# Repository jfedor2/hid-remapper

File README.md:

# HID Remapper

_For user documentation please see the project's website at [remapper.org](https://www.remapper.org/)._

This is a configurable USB dongle that allows you to remap inputs from mice, keyboards and other devices. It works completely in hardware and requires no software running on the computer during normal use.

It can do things like reassign buttons, change keyboard layouts, map mouse buttons to keyboard inputs, map keystrokes to mouse inputs, change mouse sensitivity (permanently or when a button is held), rotate mouse axes by arbitrary (non-90 degree) angles, drag-lock for mouse buttons, scroll by moving the mouse, and much more.

It is configurable [through a web browser](https://www.remapper.org/config/) using WebHID (Chrome or Chrome-based browser required).

Wireless receivers are supported and multiple devices can be connected at the same time using a USB hub (with different mappings for each device if desired).

In addition to the remapping functionality, it can do polling rate overclocking up to 1000 Hz.

A separate [serial](SERIAL.md) version of the remapper takes inputs from a serial (RS-232) mouse and translates them to USB.

There's also a [Bluetooth](BLUETOOTH.md) version that runs on nRF52840-based boards, which translates Bluetooth inputs to USB.

## How to make the device

There are three main ways of making the HID Remapper. You can either buy [this board](https://www.adafruit.com/product/5723) from Adafruit, make it yourself using a Raspberry Pi Pico (or two), or you can use the provided files to manufacture a custom board at JLCPCB or a similar service. The functionality is the same in all cases.

If you get the Feather RP2040 USB Host board from Adafruit, the device is ready to use, you just need to flash it with the right firmware ([remapper\_feather.uf2](https://github.com/jfedor2/hid-remapper/releases/latest/download/remapper_feather.uf2)). Hold the "Boot" button on the board, then press the "Reset" button. A USB drive should show up on your computer. Copy the UF2 file to that drive. That's it.

See [here](HARDWARE.md) for details on how to make the Pico variants of the device and [here](custom-boards/) for details on the custom board option.

## How to use the configuration tool

A live version of the web configuration tool can be found at [remapper.org/config](https://www.remapper.org/config/).

For details on how to use it, please see the [HID Remapper Manual](https://www.remapper.org/manual/).

If you can't use the browser-based configuration tool, there's also a [command-line tool](config-tool) that takes JSON in the same format as the web tool on standard input. I only tested it on Linux, but in theory it should also run on Windows and Mac.

## How to update the firmware

The procedure to update the firmware is similar on all variants. When you go to the configuration website and try to connect to your device when it doesn't have the latest firmware, you will get a message and a link to a version of the configuration interface that is compatible with your current (old) firmware. Click that link, connect to your HID Remapper by clicking "Open device" as usual, then go to the "Actions" tab and click "Flash firmware". This will put your device in firmware flashing mode. A drive should appear on your computer. For all the RP2040-based variants, the drive will be named "RPI-RP2". For the Bluetooth variants, it will be called something else, depending on what board you're using. Download the correct firmware file for your variant (see table below) and copy it to that drive. On custom boards v1, v2, v5, v6 and v7 (dual RP2040 boards), after flashing the firmware you have to disconnect and reconnect your HID Remapper. That's it, you can go back to the regular version of the configuration interface and carry on.

_(Please note that previously a manual "Flash B side" step was required on custom boards v1, v2, v5, v6 and v7. That is no longer necessary.)_

If you're using the dual Pico variant then you need to flash the A side using the [remapper\_dual\_a.uf2](https://github.com/jfedor2/hid-remapper/releases/latest/download/remapper_dual_a.uf2) file as described above and then flash the B side manually. Disconnect your HID Remapper from your computer, disconnect the OTG adapter from the B-side Pico, hold the BOOTSEL button on the B-side Pico and then, while holding the button, connect the B-side Pico to your computer. A drive named "RPI-RP2" should appear. Copy the [remapper\_dual\_b.uf2](https://github.com/jfedor2/hid-remapper/releases/latest/download/remapper_dual_b.uf2) file to that drive. Disconnect the B-side Pico from your computer, reconnect the OTG adapter and reconnect your HID Remapper to your computer.

When updating firmware, the current configuration on your HID Remapper is preserved. For extra peace of mind you can export your configuration to a JSON file before performing the update. That way if you need to revert to the old version of the firmware for any reason, you'll be able to import the configuration from the JSON file (configuration is lost when going from a newer firmware to an older firmware).

variant | firmware file(s) | notes
------- | ---------------- | -----------------------
single Pico | [remapper.uf2](https://github.com/jfedor2/hid-remapper/releases/latest/download/remapper.uf2) |
dual Pico | [remapper\_dual\_a.uf2](https://github.com/jfedor2/hid-remapper/releases/latest/download/remapper_dual_a.uf2)<br>[remapper\_dual\_b.uf2](https://github.com/jfedor2/hid-remapper/releases/latest/download/remapper_dual_b.uf2) | each Pico needs to be flashed separately
Feather RP2040 with USB Host | [remapper\_feather.uf2](https://github.com/jfedor2/hid-remapper/releases/latest/download/remapper_feather.uf2) |
custom board v1 | [remapper\_board.uf2](https://github.com/jfedor2/hid-remapper/releases/latest/download/remapper_board.uf2) | disconnect and reconnect after flashing
custom board v2 | [remapper\_board.uf2](https://github.com/jfedor2/hid-remapper/releases/latest/download/remapper_board.uf2) | disconnect and reconnect after flashing
custom board v3 | [remapper\_feather.uf2](https://github.com/jfedor2/hid-remapper/releases/latest/download/remapper_feather.uf2) |
custom board v4 | [remapper\_feather.uf2](https://github.com/jfedor2/hid-remapper/releases/latest/download/remapper_feather.uf2) |
custom board v5 | [remapper\_board.uf2](https://github.com/jfedor2/hid-remapper/releases/latest/download/remapper_board.uf2) | disconnect and reconnect after flashing
custom board v6 | [remapper\_board.uf2](https://github.com/jfedor2/hid-remapper/releases/latest/download/remapper_board.uf2) | disconnect and reconnect after flashing
custom board v7 | [remapper\_board\_v7.uf2](https://github.com/jfedor2/hid-remapper/releases/latest/download/remapper_board_v7.uf2) | disconnect and reconnect after flashing
custom board v8 | [remapper\_board\_v8.uf2](https://github.com/jfedor2/hid-remapper/releases/latest/download/remapper_board_v8.uf2) |
Feather nRF52840 Express | [remapper_adafruit_feather_nrf52840.uf2](https://github.com/jfedor2/hid-remapper/releases/latest/download/remapper_adafruit_feather_nrf52840.uf2) |
Xiao nRF52840 | [remapper_seeed_xiao_nrf52840.uf2](https://github.com/jfedor2/hid-remapper/releases/latest/download/remapper_seeed_xiao_nrf52840.uf2) |
serial | [remapper_serial.uf2](https://github.com/jfedor2/hid-remapper/releases/latest/download/remapper_serial.uf2) |

For boards not listed above, use the same file name you used when flashing it for the first time.

## How to compile the firmware

The easiest way to compile the firmware is to let GitHub do it for you. This repository has GitHub Actions that build the firmware, so you can just fork, make your changes, wait for the job to complete, and look for the binaries in the artifacts produced.

To compile the RP2040 firmware on your machine, use the following steps (details may vary depending on your Linux distribution):

```
sudo apt install gcc-arm-none-eabi libnewlib-arm-none-eabi libstdc++-arm-none-eabi-newlib srecord
git clone https://github.com/jfedor2/hid-remapper.git
cd hid-remapper
git submodule update --init
cd firmware
mkdir build
cd build
cmake ..
# or, to build for the custom boards:
# PICO_BOARD=remapper cmake ..
make
```

To compile the nRF52 firmware, you can either follow [Nordic's setup instructions](https://docs.nordicsemi.com/bundle/ncs-latest/page/nrf/installation.html) and then `west build -b seeed_xiao_nrf52840` to compile the firmware, or you can use Docker with a command like this (start from the top level of the repository or adjust the path accordingly):

```
docker run --rm -v $(pwd):/workdir/project -w /workdir/project/firmware-bluetooth nordicplayground/nrfconnect-sdk:v2.2-branch west build -b seeed_xiao_nrf52840
```

The nRF52 firmware can be built for `adafruit_feather_nrf52840`, `seeed_xiao_nrf52840` or `nice_nano`.

## Debugging the Bluetooth version

If a Bluetooth device connects but its inputs don't come through, start with these checks:

1. Open the Monitor tab in the [web configuration tool](https://www.remapper.org/config/) and use the device. If its inputs appear there, the Bluetooth connection is fine and the problem is in your mappings or on the USB side.
2. Make sure the device isn't also connected to something else. If it's a ZMK keyboard, unplug it from USB (or select Bluetooth output with `&out OUT_BLE`), select the profile that's paired with the remapper, and on a split keyboard pair with the central half.
3. Click "Forget all devices", remove the remapper from the device's own list of paired devices, then click "Pair new device" and pair again. A pairing that only one side remembers will fail at the encryption step.
4. If it still doesn't work, compile the debug build described below and check its LED codes.

### Debug build

In the normal firmware the LEDs stay off, except that the status LED is lit constantly in pairing mode. A debug build uses the status LED to show how far connection setup has got, and also pulses the activity LED, on boards that have one, when an input report arrives. The status LED is blue on most boards, but it's red on some nice!nano clones.

To compile it, add `-- -DREMAPPER_DEBUG_STAGES=1` to the build command:

```
docker run --rm -v $(pwd):/workdir/project -w /workdir/project/firmware-bluetooth nordicplayground/nrfconnect-sdk:v2.2-branch west build -b nice_nano -- -DREMAPPER_DEBUG_STAGES=1
```

All builds also write logs to the board's serial TX pin at 921600 baud, if you have a USB serial adapter.

### Debug build LED codes

The status LED repeats a group of slow blinks. If a step failed, a one second pause and a group of fast blinks follow. The code for a failed step stays until the next successful step or the next connection, and a single failure can clear itself if the device connects successfully afterwards.

The number of slow blinks is the last step that passed, and any fast blinks mean that the next step failed:

Slow blinks | Last step that passed | Fast blinks mean this step failed
----------- | --------------------- | ---------------------------------
1 | scanning | connecting to the device
2 | Bluetooth connection established | encryption or pairing
3 | connection encrypted | finding the device's HID service
4 | HID service found | HID setup
5 | subscribed to input reports | reading the report descriptor
6 | report descriptor read | no fast blinks at this step
7 | input report received | no fast blinks at this step

If it stays at 6 while you use the device, setup worked but the device isn't sending anything. If it reaches 7 and the Monitor tab stays empty, reports are arriving but aren't being parsed.

The number of fast blinks is the error code, capped at 30:

Code | Meaning
---- | -------
4 slow, 22 fast | the device's report types don't match their properties in a way the firmware can't correct
4 slow, 30 fast | an error code of 30 or higher, usually a HID information, report reference or protocol mode value of an unexpected size
3 slow, 2 fast | the device doesn't have a HID service
5 slow, 30 fast | the report descriptor is longer than the 512 bytes the firmware can store
4 slow, 5 or 15 fast | the device says the connection isn't secure enough (authentication or encryption)

Fast blink counts from 2 slow blinks are Zephyr's `bt_security_err` values. Other counts from 4 slow blinks are usually Bluetooth ATT error codes returned by the device.

The fast blinks are hard to count by eye, so it helps to film them. Each one takes about 0.22 seconds.

## License

The software in this repository is licensed under the [MIT License](LICENSE), unless stated otherwise.

The hardware designs in this repository are licensed under the Creative Commons Attribution 4.0 International license ([CC BY 4.0](https://creativecommons.org/licenses/by/4.0/)), unless stated otherwise.

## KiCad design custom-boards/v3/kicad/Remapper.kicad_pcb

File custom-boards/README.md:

# Custom HID Remapper boards

This document describes how to have custom HID Remapper boards manufactured using the provided design files at a service like JLCPCB. If you'd rather make the device using a Raspberry Pi Pico, see [here](../HARDWARE.md) for details on that option.

There are eight versions, imaginatively named v1-v8. v1, v2, v5, v6 and v7 are equivalent to the dual Pico variant when it comes to internal architecture and device compatibility. v3 and v4 are equivalent to the single Pico variant. v8 uses a single RP2040 chip, but it doesn't have USB inputs.

The main advantage of the v1 board is that it can be made with no soldering, you just order the board, flash the firmware, and have a working device. Files for an optional 3D printable enclosure are also available (it uses M2x8 flat head screws).

The v2 board doesn't have USB connectors and is meant to be built into existing devices like trackballs by soldering the appropriate wires directly to the board.

The v3 board has the form factor of a USB dongle (you plug it directly into your computer). It also has an LED connected to GPIO 19, which you can use as an indicator, such as whether a particular layer is active.

The v4 board has eight 3.5mm connectors wired to GPIO2-9, meant to be used with external buttons or switches. The 3D printed case for it uses two M2x4 screws and four M3x10 flat head screws.

The v5 board has a built-in four port USB hub. The 3D printed case for it uses one M2x4 screw and four M3x10 flat head screws.

The v6 board has a built-in four port USB hub and eighteen 3.5mm connectors wired to GPIO pins that can be used with external buttons or switches. The 3D printed case for it uses three M2x4 screws and four M3x10 flat head screws.

The v7 board (not pictured above) is a companion device for accessibility controllers like the PlayStation Access and the Xbox Adaptive Controller. It has four analog and ten digital outputs that can be connected to the 3.5mm input ports on those controllers. More information [here](v7).

The v8 board (not pictured above) has one 3.5mm TRRS jack that can be used for analog inputs. For example it could be used to add analog stick inputs to the Hori Flex controller. The jack also works for one or two digital buttons or switches. More information [here](v8).

## How to order the boards

The process of ordering the boards is the same for all versions. You go to JLCPCB's [website](https://jlcpcb.com/), upload the Gerber zip file, enable the "PCB Assembly" option and upload the BOM and CPL files. All the options can be left at their default values. Then click through the rest of the process, making sure that all the components are in stock.

If you want to use some other service than JLCPCB, you will likely need to adapt at least the BOM and CPL files to match their requirements.

## How to flash the firmware

### Firmware flashing mode

v1 and v3-v8 boards have buttons labeled "BOOT\_A" and "BOOT", respectively. These work the same as the BOOTSEL button on a Raspberry Pi Pico. You hold the button while connecting it to a computer to put the board in firmware flashing mode. The v2 board doesn't have a button, but it has the equivalent pin broken out. Short the BOOT pin on the A side to GND while connecting the board to a computer to put it in firmware flashing mode. Then copy the UF2 file to the drive that appears.

If the board is already flashed with some version of the HID Remapper firmware then you can also put it in firmware flashing mode by going to the web config tool and pressing the "Flash firmware" button. This is useful when you want to upgrade the firmware on a device that is not easily accessible.

When the board is fresh from the factory (has never been flashed), it should enter firmware flashing mode automatically when you connect it to a computer with no additional steps necessary.

### v1, v2, v5 and v6

Flash the board with [remapper\_board.uf2](https://github.com/jfedor2/hid-remapper/releases/latest/download/remapper_board.uf2) file by putting it in firmware flashing mode and copying the file to the "RPI-RP2" drive that should appear on your computer.

Disconnect and reconnect your HID Remapper after flashing the firmware.

_(Please note that previously a manual "Flash B side" step was required on these boards. That is no longer necessary.)_

### v7

Flash the board with [remapper\_board\_v7.uf2](https://github.com/jfedor2/hid-remapper/releases/latest/download/remapper_board_v7.uf2) file by putting it in firmware flashing mode and copying the file to the "RPI-RP2" drive that should appear on your computer.

Disconnect and reconnect your HID Remapper after flashing the firmware.

_(Please note that previously a manual "Flash B side" step was required on this board. That is no longer necessary.)_

### v3 and v4

Flash the board with [remapper\_feather.uf2](https://github.com/jfedor2/hid-remapper/releases/latest/download/remapper_feather.uf2) file by putting it in firmware flashing mode and copying the file to the "RPI-RP2" drive that should appear on your computer.

### v8

Flash the board with [remapper\_board\_v8.uf2](https://github.com/jfedor2/hid-remapper/releases/latest/download/remapper_board_v8.uf2) file by putting it in firmware flashing mode and copying the file to the "RPI-RP2" drive that should appear on your computer.

## Acknowledgements

v1, v4, v5, v6 and v7 PCB designs use [Type-C.pretty](https://github.com/ai03-2725/Type-C.pretty) library by [ai03-2725](https://github.com/ai03-2725).

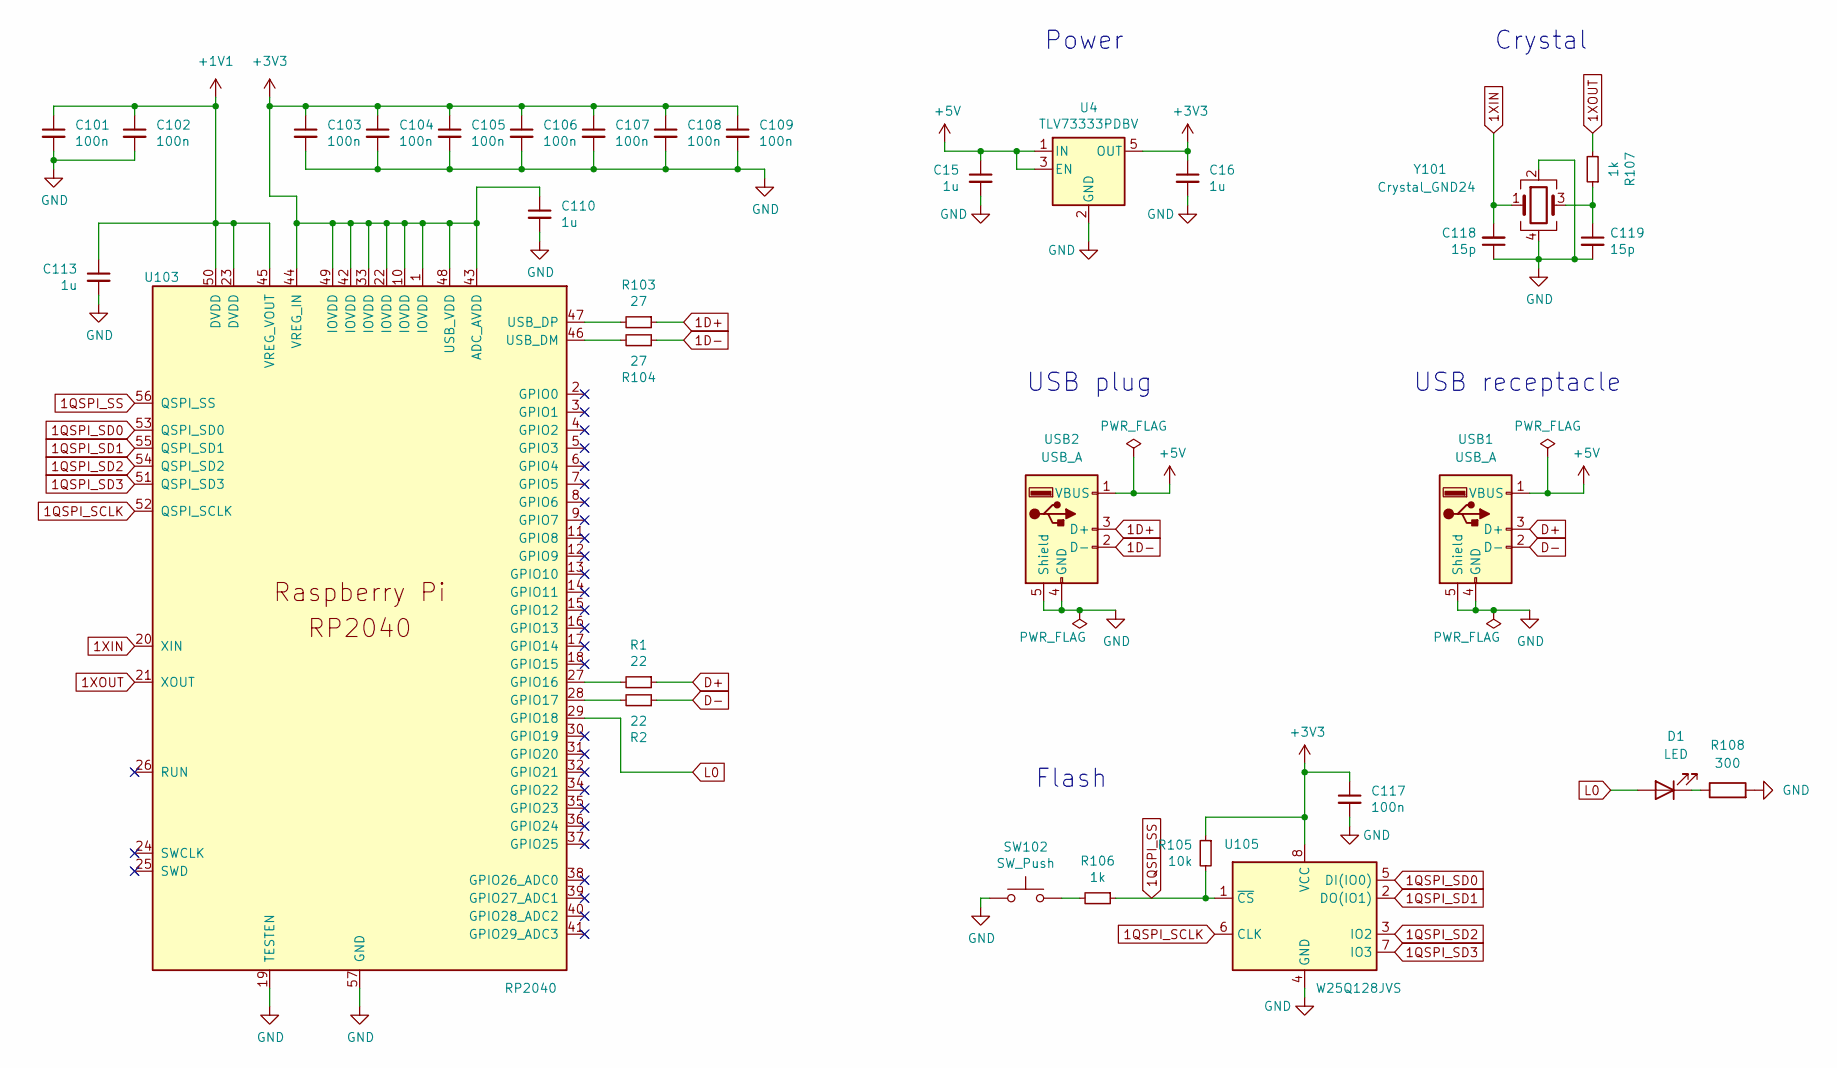
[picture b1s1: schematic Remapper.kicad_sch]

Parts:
C15, C16, C110, C113: 1u; C_0402_1005Metric; LCSC C52923
C101, C102, C103, C104, C105, C106, C107, C108, C109, C117: 100n; C_0402_1005Metric; LCSC C1525
C118, C119: 15p; C_0402_1005Metric; LCSC C1548
D1: LED; LED_0201_0603Metric
R1, R2: 22; R_0402_1005Metric; LCSC C102906
R103, R104: 27; R_0402_1005Metric; LCSC C138021
R105: 10k; R_0402_1005Metric; LCSC C25744
R106, R107: 1k; R_0402_1005Metric; LCSC C11702
R108: 300; R_0402_1005Metric
SW102: SW_Push; SW_SPST_B3U-1000P; LCSC C231329
U4: TLV73333PDBV; SOT-23-5; LCSC C134139
U103: RP2040; RP2040-QFN-56; LCSC C2040
U105: W25Q128JVS; 8-USON; LCSC C2843335
USB1: USB_A; C42459; LCSC C42459
USB2: USB_A; C98125; LCSC C98125
Y101: Crystal_GND24; Crystal_SMD_2520-4Pin_2.5x2.0mm; LCSC C90603

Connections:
1D+: R103.1, USB2.3 (D+)
1D-: R104.1, USB2.2 (D-)
1QSPI_SCLK: U103.52 (QSPI_SCLK), U105.6 (CLK)
1QSPI_SD0: U103.53 (QSPI_SD0), U105.5 (DI(IO0))
1QSPI_SD1: U103.55 (QSPI_SD1), U105.2 (DO(IO1))
1QSPI_SD2: U103.54 (QSPI_SD2), U105.3 (IO2)
1QSPI_SD3: U103.51 (QSPI_SD3), U105.7 (IO3)
1QSPI_SS: R105.2, R106.1, U103.56 (QSPI_SS), U105.1 (~CS)
1XIN: C118.2, U103.20 (XIN), Y101.1
1XOUT: R107.2, U103.21 (XOUT)
+1V1: C101.1, C102.1, C113.1, U103.23 (DVDD), U103.45 (VREG_VOUT), U103.50 (DVDD)
+3V3: C16.1, C103.1, C104.1, C105.1, C106.1, C107.1, C108.1, C109.1, C110.1, C117.1, R105.1, U4.5 (OUT), U103.1 (IOVDD), U103.10 (IOVDD), U103.22 (IOVDD), U103.33 (IOVDD), U103.42 (IOVDD), U103.43 (ADC_AVDD), U103.44 (VREG_IN), U103.48 (USB_VDD), U103.49 (IOVDD), U105.8 (VCC)
+5V: C15.1, U4.1 (IN), U4.3 (EN), USB1.1 (VBUS), USB2.1 (VBUS)
D+: R1.1, USB1.3 (D+)
D-: R2.1, USB1.2 (D-)
GND: C15.2, C16.2, C101.2, C102.2, C103.2, C104.2, C105.2, C106.2, C107.2, C108.2, C109.2, C110.2, C113.2, C117.2, C118.1, C119.2, R108.2, SW102.1, U4.2 (GND), U103.19 (TESTEN), U103.57 (GND), U105.4 (GND), USB1.4 (GND), USB1.5 (Shield), USB2.4 (GND), USB2.5 (Shield), Y101.2, Y101.4
L0: D1.2 (A), U103.29 (GPIO18), U103.30 (GPIO19)
unnamed: C119.1, R107.1, Y101.3
unnamed: D1.1 (K), R108.1
unnamed: R106.2, SW102.2
unnamed: R1.2, U103.27 (GPIO16)
unnamed: R2.2, U103.28 (GPIO17)
unnamed: R104.2, U103.46 (USB_DM)
unnamed: R103.2, U103.47 (USB_DP)

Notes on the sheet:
USB receptacle
Crystal
USB plug
Power
Flash

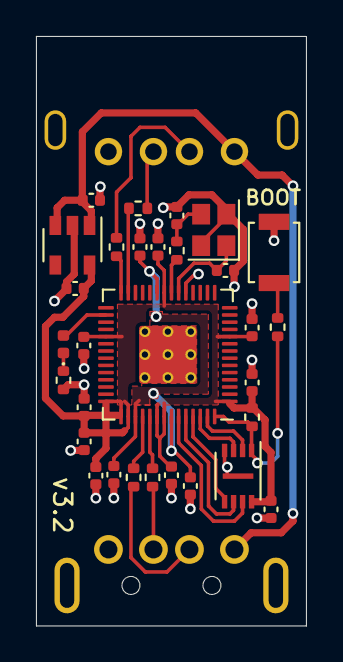
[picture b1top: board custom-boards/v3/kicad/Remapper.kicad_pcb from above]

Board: 2 copper layers, 15.0 x 32.8 mm, 32 parts (0 on the bottom side), 24 nets.

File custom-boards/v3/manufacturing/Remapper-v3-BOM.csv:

Comment,Designator,Footprint,LCSC
"100n","C101,C102,C103,C104,C105,C106,C107,C108,C109,C117","Capacitor_SMD:C_0402_1005Metric","C1525"
"15p","C118,C119","Capacitor_SMD:C_0402_1005Metric","C1548"
"1u","C15,C16,C110,C113","Capacitor_SMD:C_0402_1005Metric","C52923"
"22","R1,R2","Resistor_SMD:R_0402_1005Metric","C102906"
"27","R103,R104","Resistor_SMD:R_0402_1005Metric","C138021"
"10k","R105","Resistor_SMD:R_0402_1005Metric","C25744"
"1k","R106,R107","Resistor_SMD:R_0402_1005Metric","C11702"
"SW_Push","SW102","Button_Switch_SMD:SW_SPST_B3U-1000P","C231329"
"RP2040","U103","RP2040:RP2040-QFN-56","C2040"
"W25Q128JVS","U105","USON:8-USON","C401667"
"TLV73333PDBV","U4","SOT-23-5:SOT-23-5","C134139"
"USB_A","USB1","Type-A:C42459","C42459"
"USB_A","USB2","Type-A:C98125","C98125"
"Crystal_GND24","Y101","Crystal:Crystal_SMD_2520-4Pin_2.5x2.0mm","C90603"

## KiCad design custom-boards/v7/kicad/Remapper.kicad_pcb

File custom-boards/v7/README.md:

# HID Remapper custom board v7

This variant of HID Remapper is meant to be a companion device for accessibility controllers like the PlayStation Access controller and the Xbox Adaptive Controller, especially the former, since it lacks its own USB inputs.

It has fourteen 3.5mm output ports, four of which are analog outputs. Two of the analog outputs can be used for analog sticks and the other two for analog triggers.

The way it would typically be used is you would plug some USB input device like a joystick into one of the USB ports and then configure HID Remapper to map the axes from this joystick to analog outputs. Then you would connect the analog output port on HID Remapper to a 3.5mm input port on the PlayStation Access controller with a TRRS cable. Similarly you could map buttons on your joystick to digital HID Remapper outputs (GPIOs). The ports on the PlayStation Access controller can all work as joysticks, triggers and buttons, but on HID Remapper you have to use the dedicated ports for each.

In this case the USB-C port on HID Remapper is only used for powering it and configuration. It has to be plugged into something for the device to have power, but it doesn't have to be your PS5. You can have it plugged into a PC and change the configuration on the fly, while testing it on your console in real time.

Of course you can make use of all the mapping capabilities of HID Remapper, you can connect multiple USB devices, including mice and keyboards, and configure the mappings the way you like. The only limitation is that the PlayStation Access controller only has four 3.5mm ports so even you have two of them, you're still limited to eight ports in total.

The 3D printed case uses three M2x4 screws and four M3x10 flat head screws.

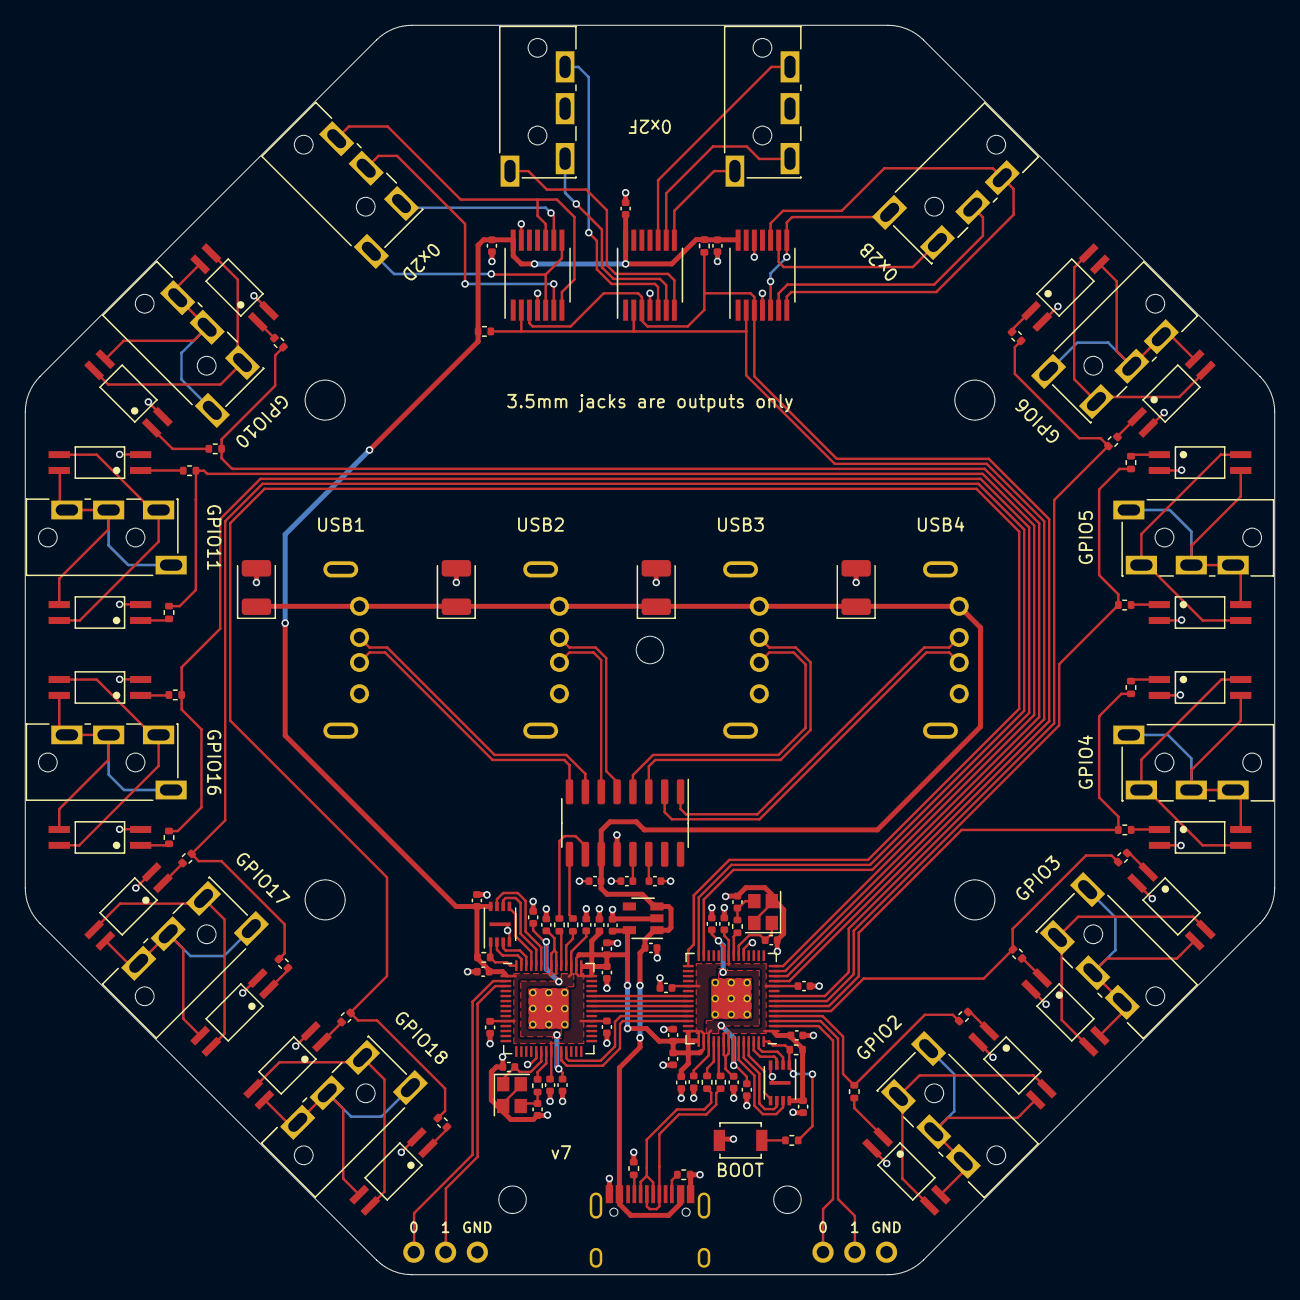
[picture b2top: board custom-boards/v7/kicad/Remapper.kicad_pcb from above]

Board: 2 copper layers, 100.0 x 100.0 mm, 133 parts (0 on the bottom side), 120 nets.

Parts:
C1, C2, C3, C4, C5, C6, C7, C8, C9, C11, C12, C14, C17, C101, C102, C103, C104, C105, C106, C107, C108, C109, C117: 100n; C_0402_1005Metric
C10, C13, C15, C16, C110, C113: 1u; C_0402_1005Metric
C18, C19, C118, C119: 15p; C_0402_1005Metric
C201, C202, C203, C204: 100u; CP_EIA-3528-21_Kemet-B
C205, C206, C207: 10u; C_0402_1005Metric
H1, H2, H3, H4: MountingHole; MountingHole_3.2mm_M3
H5, H6, H7: MountingHole; MountingHole_2.2mm_M2
J1, J2, J3, J4, J5, J6, J7, J8, J9, J10, J11, J12, J13, J14: AudioJack4; C136687
J15, J16: Conn_01x03_Pin; PinHeader_1x03_P2.54mm_Vertical
R1, R2, R6, R8, R9, R10, R11, R12, R13, R14, R17, R18, R19, R20, R21, R22, R23, R24, R25, R26: 470; R_0402_1005Metric
R3, R4, R103, R104: 27; R_0402_1005Metric
R5, R105: 10k; R_0402_1005Metric
R7, R106, R107: 1k; R_0402_1005Metric
R15, R16: 4.7k; R_0402_1005Metric
R101, R102: 5.1k; R_0402_1005Metric
SW102: SW_Push; SW_SPST_B3U-1000P
U1: SL2.1A; SOP-16_3.9x9.9mm_P1.27mm
U2, U6, U7: MCP4651; TSSOP-14
U3, U103: RP2040; RP2040-QFN-56
U4: TLV73333PDBV; SOT-23-5
U5, U105: W25Q16JVUXIQ; 8-USON
U8, U9, U10, U11, U12, U13, U14, U15, U16, U17, U18, U19, U20, U21, U22, U23, U24, U25, U26, U27: EL3H7-G; SOP-4-1.27mm
USB1, USB2, USB3, USB4: USB_A; C2689978
USB101: HRO-TYPE-C-31-M-12; HRO-TYPE-C-31-M-12-Assembly
Y1, Y101: Crystal_GND24; Crystal_SMD_2520-4Pin_2.5x2.0mm

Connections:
1D+: R103.1, USB101.6 (DP1), USB101.8 (DP2)
1D-: R104.1, USB101.5 (DN2), USB101.7 (DN1)
1QSPI_SCLK: U103.52 (QSPI_SCLK), U105.6 (CLK)
1QSPI_SD0: U103.53 (QSPI_SD0), U105.5 (DI(IO0))
1QSPI_SD1: U103.55 (QSPI_SD1), U105.2 (DO(IO1))
1QSPI_SD2: U103.54 (QSPI_SD2), U105.3 (IO2)
1QSPI_SD3: U103.51 (QSPI_SD3), U105.7 (IO3)
1QSPI_SS: R105.2, R106.1, U103.56 (QSPI_SS), U105.1 (~CS)
1XIN: C118.2, U103.20 (XIN), Y101.1
1XOUT: R107.2, U103.21 (XOUT)
+1V1: C1.1, C2.1, C13.1, U3.23 (DVDD), U3.45 (VREG_VOUT), U3.50 (DVDD)
+1V2: C101.1, C102.1, C113.1, U103.23 (DVDD), U103.45 (VREG_VOUT), U103.50 (DVDD)
+3V3: C3.1, C4.1, C5.1, C6.1, C7.1, C8.1, C9.1, C10.1, C11.1, C12.1, C14.1, C16.1, C17.1, C103.1, C104.1, C105.1, C106.1, C107.1, C108.1, C109.1, C110.1, C117.1, R5.1, R15.1, R16.1, R105.1, U2.14 (VDD), U3.1 (IOVDD), U3.10 (IOVDD), U3.22 (IOVDD), U3.33 (IOVDD), U3.42 (IOVDD), U3.43 (ADC_AVDD), U3.44 (VREG_IN), U3.48 (USB_VDD), U3.49 (IOVDD), U4.5 (OUT), U5.8 (VCC), U6.14 (VDD), U7.14 (VDD), U103.1 (IOVDD), U103.10 (IOVDD), U103.22 (IOVDD), U103.33 (IOVDD), U103.42 (IOVDD), U103.43 (ADC_AVDD), U103.44 (VREG_IN), U103.48 (USB_VDD), U103.49 (IOVDD), U105.8 (VCC)
+5V: C15.1, C201.1, C202.1, C203.1, C204.1, C207.1, U1.11 (VDD5), U4.1 (IN), U4.3 (EN), USB1.1 (VBUS), USB2.1 (VBUS), USB3.1 (VBUS), USB4.1 (VBUS), USB101.2 (VBUS), USB101.11 (VBUS)
A_GPIO0: J15.1, U103.2 (GPIO0)
A_GPIO1: J15.2, U103.3 (GPIO1)
B_GPIO0: J16.1, U3.2 (GPIO0)
B_GPIO1: J16.2, U3.3 (GPIO1)
CTS1RTS: U3.38 (GPIO26_ADC0), U103.35 (GPIO23)
D+: R3.1, U1.10 (DP)
D-: R4.1, U1.9 (DM)
DM1: U1.7 (DM1), USB1.2 (D-)
DM2: U1.5 (DM2), USB2.2 (D-)
DM3: U1.3 (DM3), USB3.2 (D-)
DM4: U1.1 (DM4), USB4.2 (D-)
DP1: U1.8 (DP1), USB1.3 (D+)
DP2: U1.6 (DP2), USB2.3 (D+)
DP3: U1.4 (DP3), USB3.3 (D+)
DP4: U1.2 (DP4), USB4.3 (D+)
GND: C1.2, C2.2, C3.2, C4.2, C5.2, C6.2, C7.2, C8.2, C9.2, C10.2, C11.2, C12.2, C13.2, C14.2, C15.2, C16.2, C17.2, C18.1, C19.2, C101.2, C102.2, C103.2, C104.2, C105.2, C106.2, C107.2, C108.2, C109.2, C110.2, C113.2, C117.2, C118.1, C119.2, C201.2, C202.2, C203.2, C204.2, C205.2, C206.2, C207.2, J15.3, J16.3, R101.2, R102.2, SW102.1, U1.12 (GND), U2.4 (VSS), U2.13 (A1), U3.19 (TESTEN), U3.57 (GND), U4.2 (GND), U5.4 (GND), U6.4 (VSS), U6.12 (A2), U7.4 (VSS), U8.2, U9.2, U10.2, U11.2, U12.2, U13.2, U14.2, U15.2, U16.2, U17.2, U18.2, U19.2, U20.2, U21.2, U22.2, U23.2, U24.2, U25.2, U26.2, U27.2, U103.19 (TESTEN), U103.57 (GND), U105.4 (GND), USB1.4 (GND), USB1.5 (Shield), USB2.4 (GND), USB2.5 (Shield), USB3.4 (GND), USB3.5 (Shield), USB4.4 (GND), USB4.5 (Shield), USB101.1 (GND), USB101.12 (GND), USB101.13 (SHIELD), Y1.2, Y1.4, Y101.2, Y101.4
JACK1: R1.1, R17.1, U103.29 (GPIO18)
JACK2: R2.1, R6.1, U103.28 (GPIO17)
JACK3: R8.1, R9.1, U103.27 (GPIO16)
JACK4: R10.1, R11.1, U103.14 (GPIO11)
JACK5: R12.1, R13.1, U103.13 (GPIO10)
JACK6_R1: J1.R1, U2.6 (P1W)
JACK6_R2: J1.R2, U2.7 (P1A), U2.10 (P0B)
JACK6_S: J1.S, U2.5 (P1B), U2.8 (P0A)
JACK6_T: J1.T, U2.9 (P0W)
JACK7_R2: J3.R2, U7.5 (P1B)
JACK7_S: J3.S, U7.7 (P1A)
JACK7_T: J3.T, U7.6 (P1W)
JACK8_R2: J4.R2, U7.10 (P0B)
JACK8_S: J4.S, U7.8 (P0A)
JACK8_T: J4.T, U7.9 (P0W)
JACK9_R1: J2.R1, U6.6 (P1W)
JACK9_R2: J2.R2, U6.7 (P1A), U6.10 (P0B)
JACK9_S: J2.S, U6.5 (P1B), U6.8 (P0A)
JACK9_T: J2.T, U6.9 (P0W)
JACK10: R14.1, R18.1, U103.8 (GPIO6)
JACK11: R19.1, R20.1, U103.7 (GPIO5)
JACK12: R21.1, R22.1, U103.6 (GPIO4)
JACK13: R23.1, R24.1, U103.5 (GPIO3)
JACK14: R25.1, R26.1, U103.4 (GPIO2)
unnamed: C19.1, R7.1, Y1.3
unnamed: C119.1, R107.1, Y101.3
unnamed: J5.R1, J5.R2, J5.S, U8.4, U9.3
unnamed: J5.T, U8.3, U9.4
unnamed: J6.R1, J6.R2, J6.S, U10.4, U11.3
unnamed: J6.T, U10.3, U11.4
unnamed: J7.R1, J7.R2, J7.S, U12.4, U13.3
unnamed: J7.T, U12.3, U13.4
unnamed: J8.R1, J8.R2, J8.S, U14.4, U15.3
unnamed: J8.T, U14.3, U15.4
unnamed: J9.R1, J9.R2, J9.S, U16.4, U17.3
unnamed: J9.T, U16.3, U17.4
unnamed: J10.R1, J10.R2, J10.S, U18.4, U19.3
unnamed: J10.T, U18.3, U19.4
unnamed: J11.R1, J11.R2, J11.S, U20.4, U21.3
unnamed: J11.T, U20.3, U21.4
unnamed: J12.R1, J12.R2, J12.S, U22.4, U23.3
unnamed: J12.T, U22.3, U23.4
unnamed: J13.R1, J13.R2, J13.S, U24.4, U25.3
unnamed: J13.T, U24.3, U25.4
unnamed: J14.R1, J14.R2, J14.S, U26.4, U27.3
unnamed: J14.T, U26.3, U27.4
unnamed: R1.2, U9.1
unnamed: R2.2, U10.1
unnamed: R6.2, U11.1
unnamed: R8.2, U12.1
unnamed: R9.2, U13.1
unnamed: R10.2, U14.1
unnamed: R11.2, U15.1
unnamed: R12.2, U16.1
unnamed: R13.2, U17.1
unnamed: R14.2, U18.1
unnamed: R17.2, U8.1
unnamed: R18.2, U19.1
unnamed: R19.2, U20.1
unnamed: R20.2, U21.1
unnamed: R21.2, U22.1
unnamed: R22.2, U23.1
unnamed: R23.2, U24.1
unnamed: R24.2, U25.1
unnamed: R25.2, U26.1
unnamed: R26.2, U27.1
unnamed: R106.2, SW102.2
unnamed: C206.1, U1.14 (VDD18)
unnamed: C205.1, U1.13 (VDD33)
unnamed: R4.2, U3.46 (USB_DM)
unnamed: R3.2, U3.47 (USB_DP)
unnamed: R104.2, U103.46 (USB_DM)
unnamed: R103.2, U103.47 (USB_DP)
unnamed: R102.1, USB101.4 (CC1)
unnamed: R101.1, USB101.10 (CC2)
QSPI_SCLK: U3.52 (QSPI_SCLK), U5.6 (CLK)
QSPI_SD0: U3.53 (QSPI_SD0), U5.5 (DI(IO0))
QSPI_SD1: U3.55 (QSPI_SD1), U5.2 (DO(IO1))
QSPI_SD2: U3.54 (QSPI_SD2), U5.3 (IO2)
QSPI_SD3: U3.51 (QSPI_SD3), U5.7 (IO3)
QSPI_SS: R5.2, U3.56 (QSPI_SS), U5.1 (~CS)
RTS1CTS: U3.35 (GPIO23), U103.38 (GPIO26_ADC0)
RX1TX: U3.37 (GPIO25), U103.36 (GPIO24)
SCL: R15.2, U2.2 (SCL), U6.2 (SCL), U7.2 (SCL), U103.12 (GPIO9)
SDA: R16.2, U2.3 (SDA), U6.3 (SDA), U7.3 (SDA), U103.11 (GPIO8)
SWCLK: U3.24 (SWCLK), U103.40 (GPIO28_ADC2)
SWD: U3.25 (SWD), U103.39 (GPIO27_ADC1)
TX1RX: U3.36 (GPIO24), U103.37 (GPIO25)
XIN: C18.2, U3.20 (XIN), Y1.1
XOUT: R7.2, U3.21 (XOUT)

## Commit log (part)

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2023-10-03 Rephrase web config tool text
2023-10-07 Workaround for Xbox Adaptive Controller BLE UUIDs
    This is a workaround for the Xbox Adaptive Controller that sends UUIDs
    like this: 00002a4a-0000-0000-0000-000000000000 in Find Information
    responses.
    This is not the correct UUID128 representation for UUID16(2a4a), which
    would be: 00002a4a-0000-1000-8000-00805f9b34fb.
2023-10-18 MIDI input over USB
    This adds support for reading MIDI inputs over USB.
    Note on, polyphonic key pressure, control change, channel pressure,
    program and pitch bend are mapped to 0xfff7xxxx usages.
    Note off sets the "note on" usage state to zero, discarding the note
    off velocity.
2023-11-08 GPIO outputs
    Adds the possibility to set a GPIO pin as the target of a mapping.
    Also makes all otherwise unused pins available for input/output
    (previously limited to GPIO2-GPIO9).
2023-11-15 GPIO output high impedance mode
    Previously GPIO output pins were set to low when the output value was
    0 and high when the output value was 1.
    This commit adds a second mode in which the GPIO pin is set to high
    impedance when the output value is 0 and to low when the output value
    is 1.
    This should make it easier to use the GPIO outputs as inputs on other
2023-12-13 Remove future goals from README
2023-12-13 Prevent macros from overflowing the output buffer
    When we introduced macro step duration, we got rid of checking if the
    output report queue is empty before executing the next step of the
    macro.
    Under certain circumstances this can overflow the output buffer,
    dropping inputs.
    We bring the check back. This will sometimes mean that the actual
2023-12-13 Add build for Waveshare RP2040-PiZero
    https://www.waveshare.com/rp2040-pizero.htm
2023-12-30 Per-device mappings
    This commit introduces the possibility of having separate mappings for
    devices connected to each port on a USB hub.
    Each mapping now has an additional "source_port" attribute that
    decides which input state this mapping should read. When it's set to
    0, it behaves as it did previously, taking the cumulative input state
    from all devices. When nonzero, it only takes the input state from the
2024-01-02 Ignore usages past 64 bytes in the report
    This commit makes it so that the report descriptor parser doesn't
    store information about usages located beyond 64 bytes in the report.
    We're not currently handling reports longer than 64 bytes anyway and
    this protects us from running out of memory on some broken report
    descriptors with thousands of declared usages.
2024-01-09 Handle keyboard RollOver
    Some keyboards can't handle certain combinations of keys being pressed
    (because of hardware or report descriptor limitations). When they
    detect a situation like this they send a special usage code
    (0x00070001). When we see this usage we now ignore the entire report.
    There's nothing we can do about the keyboard's limitations but at
    least now when it happens it doesn't look like the user released some
2024-01-09 Make "hold" mappings work with macros
    Mappings with the "hold" flag set and a macro as the output now work.
2024-04-08 Change available remap layers to 12
    Change available remap layers to 12
2024-04-09 Make hold+sticky mappings work
    This makes it so that mappings with both the "hold" flag and the
    "sticky" flag now work as expected, including when used for activating
    layers.
2024-04-09 Custom board v6 and v7 case variants with labels
    This adds alternate versions of the 3D printable models for custom
    board v7 and v8 enclosures.
    The variants differ in that they have labels for the USB ports and
    the GPIO pins that are wired to the 3.5mm jacks.
2024-04-09 Fix for zero values not being sent to digipots
    Output values are only written out if they're non-zero, which works
    because outgoing input reports are set to all zeros before every
    iteration.
    Analog outputs are not part of the outgoing input reports and weren't
    set to zero before every iteration, which resulted in zero values never
    being sent to the digital potentiometers.
2024-04-09 Ignore empty input reports
    Some devices occasionally send empty input reports for whatever reason.
    Because of how we currently read reports, an empty report was
    interpreted as all inputs set to zero values.
    To avoid this issue, just ignore empty reports.
2024-04-09 Increase number of layers to 8
    This increases the number of layers to 8 internally.
    The additional layers are currently hidden in the configuration UI.
2024-04-09 Add firmware info for custom board v8
2024-04-17 try report desc without array
2024-04-18 New example: one-handed keyboard layout
2024-04-19 add desc to the same place
2024-04-23 Add example: one button drag-lock (two variants)
2024-05-01 Don't reset scroll resolution multiplier on mount
2024-05-22 Add boot protocol keyboard support
    This makes it so that we can act as a keyboard in boot protocol mode.
    The default is report protocol mode and the host can request a switch
    to boot protocol. We revert to report protocol on (re-)mount.
2024-05-22 Fix for expressions longer than 255 ops
    Bumps config version to 13.
2024-05-22 Add example: scroll wheel smoothly adjusts DPI
2024-05-28 hub_port in Bluetooth version
2024-05-29 Sanitize outgoing reports
    This adds the option for an emulated device type to sanitize input
    reports ensuring values are valid before the report is sent out.
    Currently used to clamp Stadia stick axes to 1-255.
2024-06-24 Update release.yml
    Added Manual Workflow Run
2024-06-27 Update nRF Connect SDK documentation URL
2024-07-09 New example: keyboard to XAC compatible adapter
2024-08-11 Add info on updating firmware to README
2024-08-25 New example: turbo
2024-10-02 Prevent open/load/save while another is running
    Makes it so that pressing "Open device", "Load from device", "Save to
    device" buttons on the configuration website does nothing if another
    operation is still running.
2024-10-14 New expression op: IFTE
2024-10-14 New expression op: MONITOR
2024-10-14 New expression op: PRINT_IF
2024-10-14 Avoid get_state_ptr() call in expressions
    This speeds up expression evaluation a bit by avoiding the call to
    get_state_ptr() in operations that fetch input states.
    If an input_state (prev_input_state, etc.) op is immediately preceded
    by a usage constant, the pointer to the input state is saved in the
    expression element structure.
2024-10-14 Add Pico 2 builds
2024-10-17 Add more axes and buttons to XAC/Flex mode
2024-11-03 init rp2040_zero board, fix wrong uart pins for zero boards
2024-11-03 commenting the build action for everything except the single version firmware.
2024-11-06 Add advanced custom board v8 analog stick example
    This example auto-calibrates the neutral point and axis ranges.
    It also has a proper radial deadzone.
2024-11-19 Set defaults for digipot values
    On custom board v7, Analog 0/1 and 2/3 are meant for sticks and 4 and
    5 for triggers, so hardwire the default values according to that.
    Worry about making it generic later.
2024-11-19 New expression op: PLUGGED_IN
    Puts 1 on the stack if something is plugged into the currently
    selected hub port, 0 otherwise.
    If selected port is 0 ("all ports"), puts 1 on the stack regardless of
    what is plugged in.
2024-12-02 Make multiple mappings for the same stick work better
    Previously when we had multiple mappings with the same stick axis as
    the target, we would select one of the sources that was in a
    non-neutral position with no control over what happens when there's
    more than one. This doesn't work very well because some sticks don't
    stay at precisely 128 when neutral. In practice if we wanted such
    mappings, we had to use expressions and handle it ourselves.
2024-12-02 Mouse/gamepad source labels
    Adds a setting on the configuration website to choose between mouse
    and gamepad labels for source usages on a mapping.
    This is needed because for mappings we only consider usages, not the
    collections they appear in, and for example mouse X/Y axis is the same
    usage as left stick X/Y on a game controller. Similarly the first few
    button usages on a mouse have assigned meanings like left/right button
2024-12-02 Fallback "Button X" labels for all buttons
2024-12-02 Fallback source usages names
    Adds a list of source usages that are not displayed in the modal, but
    if mappings with those usages exist, they can get a readable label.
    It includes the non-overlapping usages from the mouse/gamepad sets (so
    that the non-conflicting usages get proper labels even if the set they
    belong to is not the currently selected one) and some alternative
    gamepad trigger usages.
2024-12-08 Fallback SOF timer
    Setup a timer to call manual_sof() again after 1050us in case we stop
    getting SOFs from host.
2025-01-03 Protect against overflow when persisting config
    Don't overflow the buffer when the persisted config doesn't fit in the
    space we have for it in flash.
2025-01-03 PERSIST_CONFIG return code
    Make it possible to check if PERSIST_CONFIG command succeeded or
    failed due to the config being too large to persist in flash.
2025-01-03 Assign all expression input state slots on demand
    Previously we assigned state slots to some, but not all, inputs used
    in expressions on configuration load, and we also did an
    "optimization" pass that stored some state pointers in expressions so
    that we didn't have to go through get_state_ptr() on every evaluation.
    Now we just do get_state_ptr() with assign_if_absent=true while
    evaluating the expressions and cache that pointer.
2025-01-15 Fix regression: PS auth
    Since we're adding the report ID to the outgoing buffer in
    do_queue_out_report() now, we shouldn't be also adding it manually in
    PS auth code.
2025-01-16 Add example: analog stick to L2/R2
2025-01-22 Fix regression: clear raw relative input states
2025-02-22 fixed targeting of board nrf52840dk_nrf52840
2025-03-10 Firmware build for Waveshare RP2350-USB-A board
2025-03-11 Use a cheaper type of LED
2025-03-22 Add a photo and information to custom board README
2025-04-03 Thicken all walls
2025-04-28 Update TinyUSB to newest version
2025-05-10 Add Custom Manuf and Product Identifiers
2025-05-10 Add instructions to compile on a Mac (Apple Silicone and Intel)
2025-05-23 Normalize gamepad inputs
    Add an option (enabled by default) to make it so that inputs coming
    from known gamepads are adjusted to make buttons from the standard
    layout show up as the same usages, matching the PlayStation/Switch
    ones.
    Currently Xbox and Stadia controllers are normalized, others can be
    added in the future.
2025-06-17 Invalidate cached state pointers in expressions
    This makes it so that the cached state pointers in expressions are
    reset when we reset all the state slot assignments.
    Not doing this wasn't an issue when we were resetting the state slots
    after a configuration save, because in that case the expressions were
    recreated anyway, but it was an issue when set_mapping_from_config()
    was called after a boot/report protocol change.
2025-07-05 imu_enabled false by default
2025-09-11 Update usages.js
    added 8 more expressions
2025-11-10 Add workflow_dispatch to build-nrf52.yml
2025-11-18 Never treat certain usages as binary
    Some devices have array range inputs in their report descriptors that
    include usages like horizontal scroll ("AC Pan", 0x000c0238) and
    sometimes even mouse/joystick axes (0x00010030 etc.).
    This caused issues for us because even though these devices also had
    these inputs listed separately as regular inputs, we were marking them
    as binary because of the array inputs.
2025-11-24 Adds intructions on how to flash nrf52840 dongle
2025-12-17 properly initialise west repo, did it wrong before
2025-12-17 firmware-bluetooth: adds support for nrf52840dongle/nrf52840
    Support with default bootloader as well
2025-12-18 Only mark port as active after we get a report
    Mappings with a hub port number set on their input side are ignored if
    nothing is plugged into that hub port, which lets us avoid glitches
    for inputs with a non-zero neutral state (like analog sticks on a game
    controller), especially when the input is an expression or a register.
    Previously we marked the hub port as active immediately after a device
    was plugged into it, which meant that we could still encounter issues
2026-01-20 Add ability to wake host from suspend
    Currently only enabled for the keyboard/mouse emulated device types
    and only on the RP2040 variant.
2026-01-30 Don't wake the host from suspend on mouse movement
    Only wake the host when we have a report with keys or buttons pressed.
    This matches real device behavior.
2026-03-20 Check-in
